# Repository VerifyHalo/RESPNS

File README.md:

# RESPonsive Neuro Stimulator

A public subset of our private development repositories.

We (re)designed an epilepsy implant in the class of NeuroPace's RNS from catalog chips, with prototype boards at about $600 in parts (60x cheaper), and run in vivo experiments to find the most effective treatment techniques.

### Background 

About 50 million people live with epilepsy, and 1 in 3 do not respond to medication. For many of them, the most advanced option is responsive neurostimulation: a real-time "surgeon" in the skull that listens to the brain (tissue), catches a seizure as it starts, and disrupts it with a short burst of stimulation. NeuroPace's RNS System, designed in the early 2000s and approved by the FDA in 2013, is still the only one, at about $37,000 for the system. It runs on a sealed, non-rechargeable cell; today's low-power chips and wireless charging make a redesign possible. In the long-term trial, patients had a median of 75% fewer seizures after 9 years.

Responsive neurostimulation (RNS) systems must be fully implanted because percutaneous components pose an infection risk, while emerging non-invasive data acquisition systems cannot match the signal quality of invasive techniques. So the battery is sealed in and every microamp counts. That is why devices like this have relied on custom chips.

### Redesign

Research prototype for bench and animal work. Not for human use.

Copyright © 2026 Anton Melnychuk. Licensed under the CERN Open Hardware Licence v2, Strongly Reciprocal (CERN-OHL-S-2.0); see LICENSE.

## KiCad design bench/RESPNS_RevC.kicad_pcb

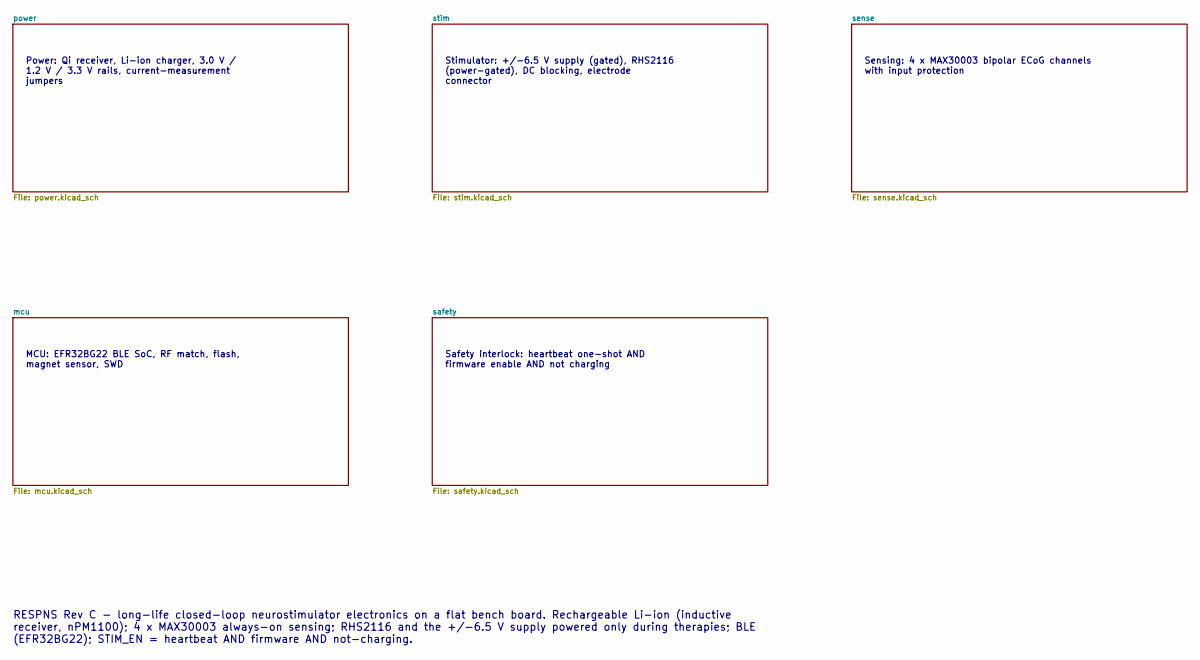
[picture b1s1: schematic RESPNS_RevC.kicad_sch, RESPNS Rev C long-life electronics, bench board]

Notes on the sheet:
Power: Qi receiver, Li-ion charger, 3.0 V / 1.2 V / 3.3 V rails, current-measurement jumpers
Stimulator: +/-6.5 V supply (gated), RHS2116 (power-gated), DC blocking, electrode connector
Sensing: 4 x MAX30003 bipolar ECoG channels with input protection
MCU: EFR32BG22 BLE SoC, RF match, flash, magnet sensor, SWD
Safety interlock: heartbeat one-shot AND firmware enable AND not charging
RESPNS Rev C - long-life closed-loop neurostimulator electronics on a flat bench board. Rechargeable Li-ion (inductive receiver, nPM1100); 4 x MAX30003 always-on sensing; RHS2116 and the +/-6.5 V supply powered only during therapies; BLE (EFR32BG22); STIM_EN = heartbeat AND firmware AND not-chargin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

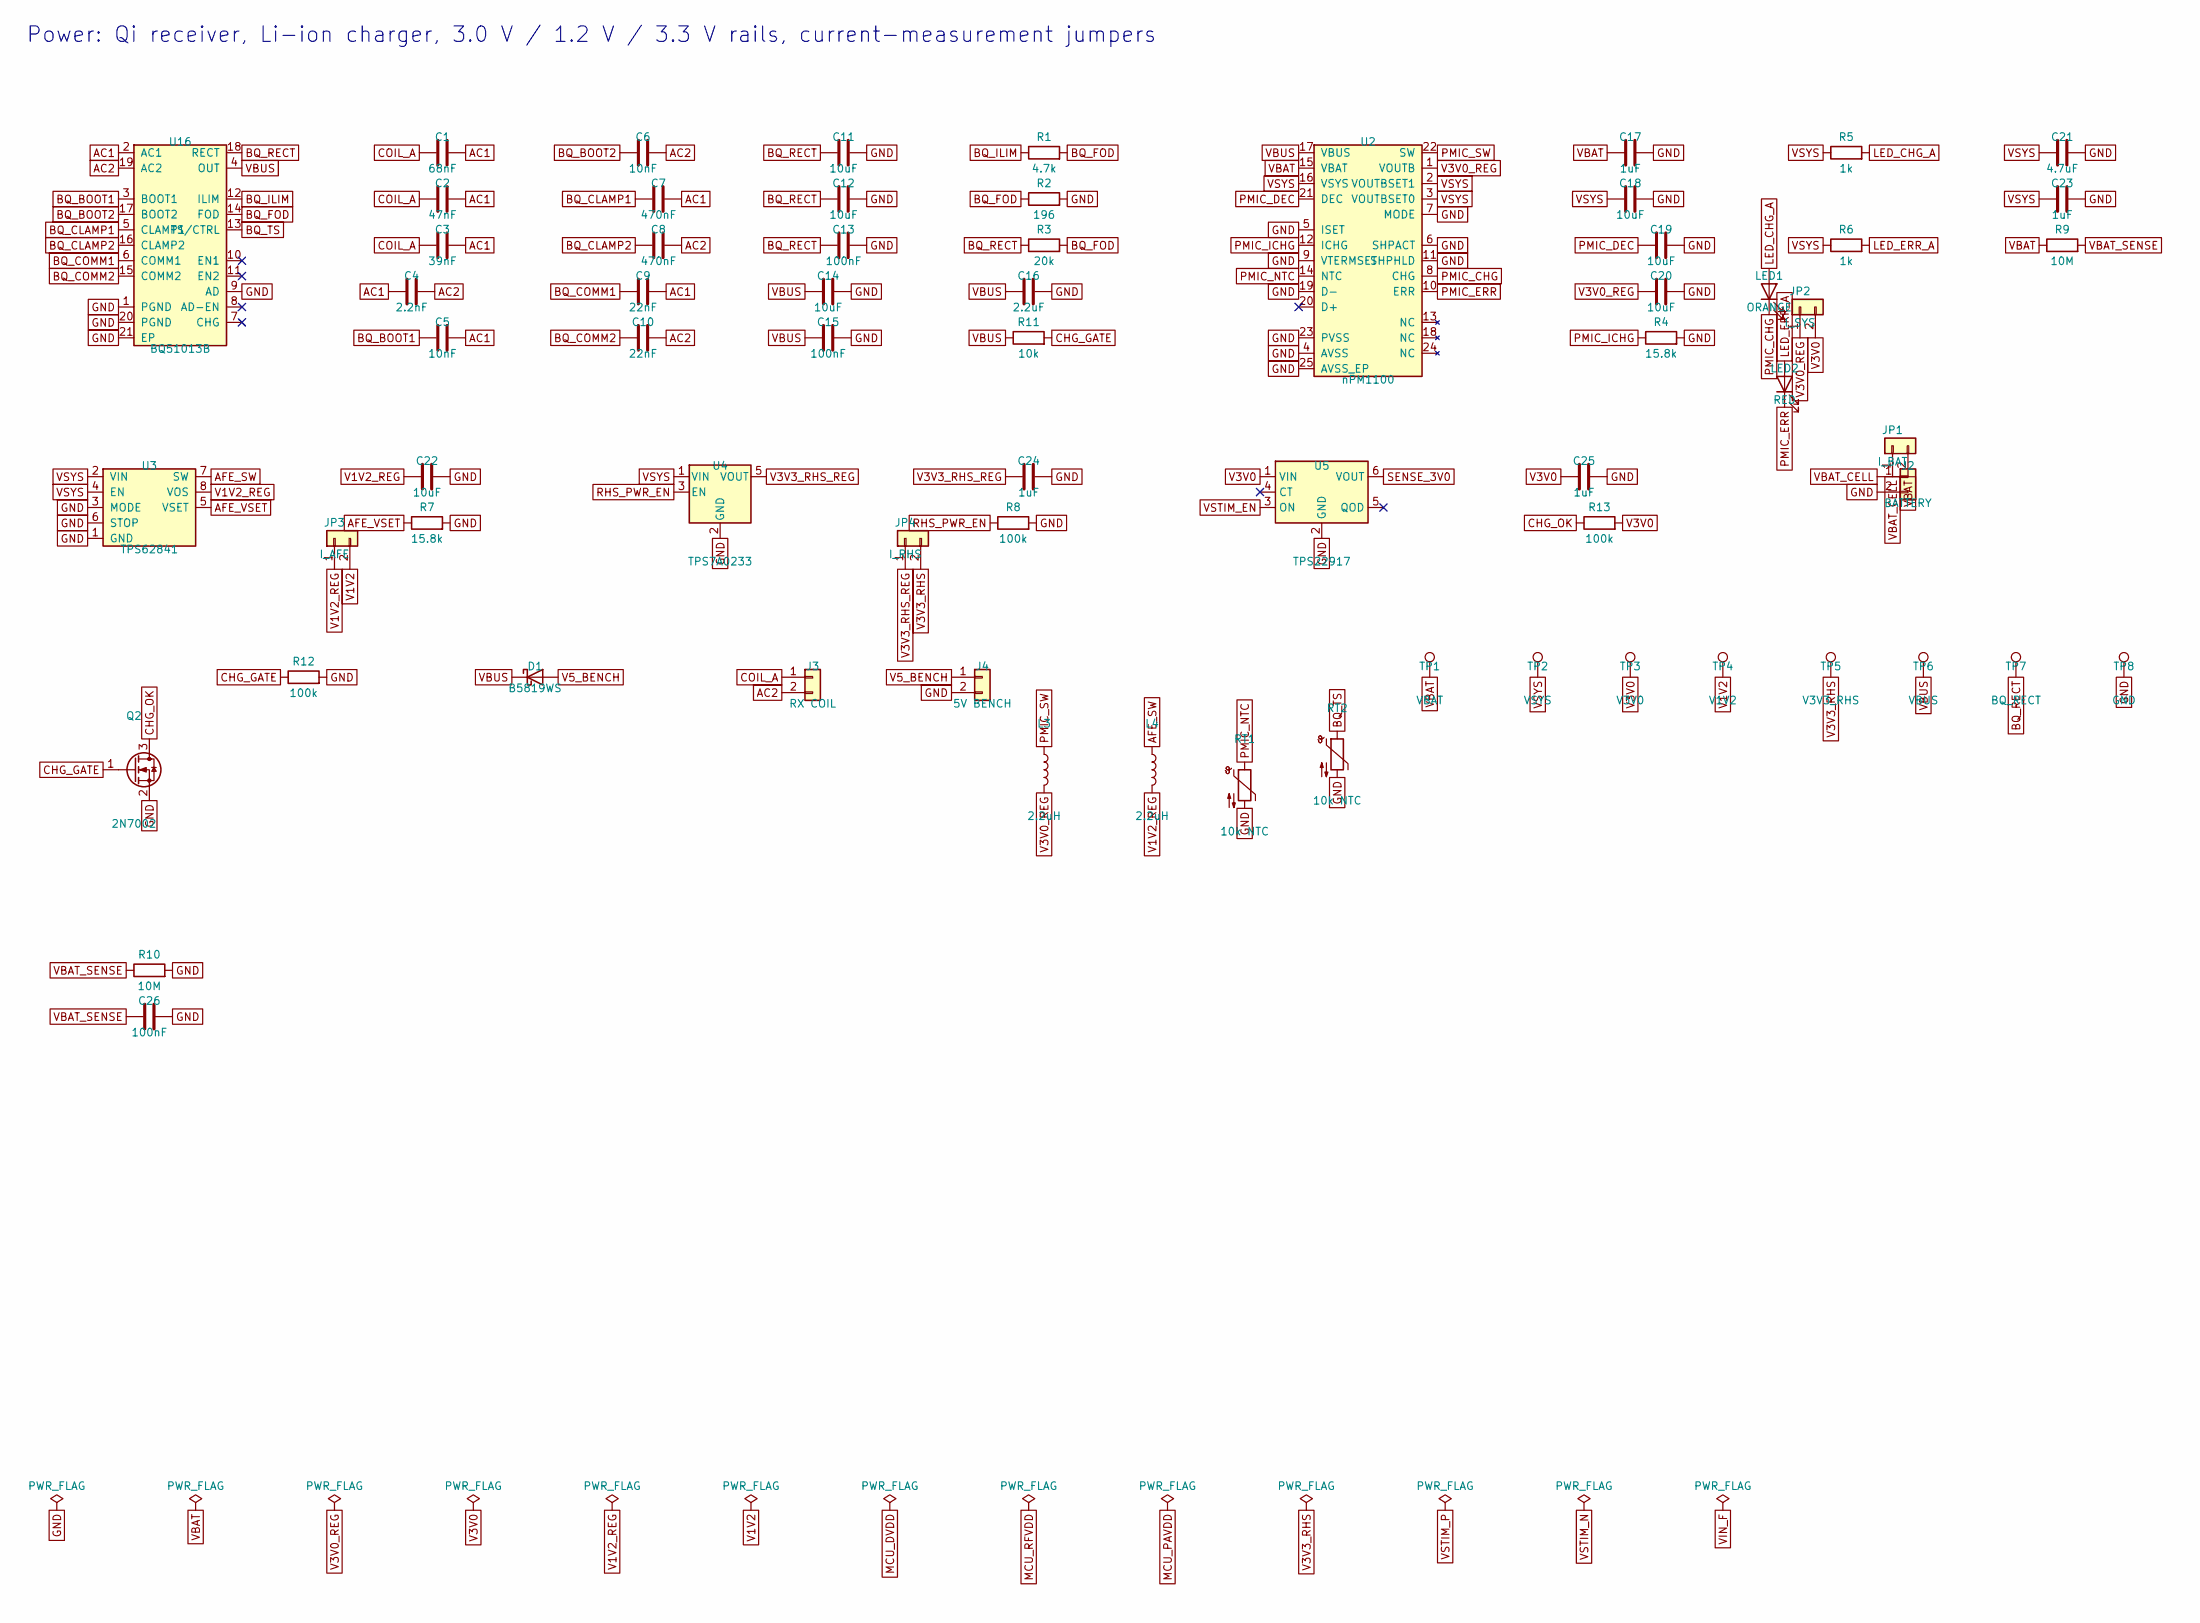
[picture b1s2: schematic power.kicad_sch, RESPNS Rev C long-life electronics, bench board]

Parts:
C1: 68nF; C_0603_1608Metric; MPN CL10B683KB8NNNC
C2: 47nF; C_0603_1608Metric; MPN CL10B473KB8NNNC
C3: 39nF; C_0603_1608Metric; MPN CL10B393KB8NNNC
C4: 2.2nF; C_0603_1608Metric; MPN CL10C222JB8NNNC
C5, C6: 10nF; C_0603_1608Metric; MPN CL10B103KB8NNNC
C7, C8: 470nF; C_0603_1608Metric; MPN CL10B474KA8NNNC
C9, C10: 22nF; C_0603_1608Metric; MPN CL10B223KB8NNNC
C11, C12, C14: 10uF; C_0805_2012Metric; MPN CL21A106KAYNNNE
C13, C15: 100nF; C_0603_1608Metric; MPN CL10B104KA8NNNC
C16: 2.2uF; C_0805_2012Metric; MPN CL21A225KAFNNNE
C17, C23, C24, C25: 1uF; C_0402_1005Metric; MPN CL05A105KA5NQNC
C18, C19, C20, C22: 10uF; C_0603_1608Metric; MPN CL10A106KP8NNNC
C21: 4.7uF; C_0603_1608Metric; MPN CL10A475KO8NNNC
C26: 100nF; C_0402_1005Metric; MPN CL05B104KO5NNNC
D1: B5819WS; D_SOD-323; MPN B5819WS
J2: BATTERY; JST_PH_S2B-PH-SM4-TB_1x02-1MP_P2.00mm_Horizontal; MPN S2B-PH-SM4-TB(LF)(SN)
J3: RX COIL; JST_SH_SM02B-SRSS-TB_1x02-1MP_P1.00mm_Horizontal; MPN SM02B-SRSS-TB(LF)(SN)
J4: 5V BENCH; PinHeader_1x02_P2.54mm_Vertical; MPN PZ254V-11-02P
JP1: I_BAT; PinHeader_1x02_P2.54mm_Vertical; MPN PZ254V-11-02P
JP2: I_SYS; PinHeader_1x02_P2.54mm_Vertical; MPN PZ254V-11-02P
JP3: I_AFE; PinHeader_1x02_P2.54mm_Vertical; MPN PZ254V-11-02P
JP4: I_RHS; PinHeader_1x02_P2.54mm_Vertical; MPN PZ254V-11-02P
L3, L4: 2.2uH; L_Changjiang_FTC201607S; MPN FTC201607S2R2MBCA
LED1: ORANGE; LED_0603_1608Metric; MPN 19-217/S2C-AL1M2VY/6T
LED2: RED; LED_0603_1608Metric; MPN 19-217/R6C-AL1M2VY/6T
Q2: 2N7002; SOT-23; MPN 2N7002
R1: 4.7k; R_0402_1005Metric; MPN 0402WGF4701TCE
R2: 196; R_0402_1005Metric; MPN 0402WGF1960TCE
R3: 20k; R_0402_1005Metric; MPN 0402WGF2002TCE
R4, R7: 15.8k; R_0402_1005Metric; MPN 0402WGF1582TCE
R5, R6: 1k; R_0402_1005Metric; MPN 0402WGF1001TCE
R8, R12, R13: 100k; R_0402_1005Metric; MPN 0402WGF1003TCE
R9, R10: 10M; R_0402_1005Metric; MPN 0402WGF1005TCE
R11: 10k; R_0402_1005Metric; MPN 0402WGF1002TCE
RT1, RT2: 10k NTC; R_0402_1005Metric; MPN NCP15XH103F03RC
TP1: VBAT; TestPoint_Pad_D1.0mm
TP2: VSYS; TestPoint_Pad_D1.0mm
TP3: V3V0; TestPoint_Pad_D1.0mm
TP4: V1V2; TestPoint_Pad_D1.0mm
TP5: V3V3_RHS; TestPoint_Pad_D1.0mm
TP6: VBUS; TestPoint_Pad_D1.0mm
TP7: BQ_RECT; TestPoint_Pad_D1.0mm
TP8: GND; TestPoint_Pad_D1.0mm
U2: nPM1100; QFN-24-1EP_4x4mm_P0.5mm_EP2.6x2.6mm_ThermalVias; MPN NPM1100-QDAA-R7
U3: TPS62841; VSON-8_1.5x2mm_P0.5mm; MPN TPS62841DLCR
U4: TPS7A0233; SOT-23-5; MPN TPS7A0233PDBVR
U5: TPS22917; SOT-23-6; MPN TPS22917DBVR
U16: BQ51013B; Texas_VQFN-RHL-20_ThermalVias; MPN BQ51013BRHLR

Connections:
AC1: C1.2, C2.2, C3.2, C4.1, C5.2, C7.2, C9.2, U16.2 (AC1)
AC2: C4.2, C6.2, C8.2, C10.2, J3.2, U16.19 (AC2)
AFE_SW: L4.1, U3.7 (SW)
AFE_VSET: R7.1, U3.5 (VSET)
BQ_BOOT1: C5.1, U16.3 (BOOT1)
BQ_BOOT2: C6.1, U16.17 (BOOT2)
BQ_CLAMP1: C7.1, U16.5 (CLAMP1)
BQ_CLAMP2: C8.1, U16.16 (CLAMP2)
BQ_COMM1: C9.1, U16.6 (COMM1)
BQ_COMM2: C10.1, U16.15 (COMM2)
BQ_FOD: R1.2, R2.1, R3.2, U16.14 (FOD)
BQ_ILIM: R1.1, U16.12 (ILIM)
BQ_RECT: C11.1, C12.1, C13.1, R3.1, TP7.1, U16.18 (RECT)
BQ_TS: RT2.1, U16.13 (TS/CTRL)
CHG_GATE: Q2.1 (G), R11.2, R12.1
CHG_OK: Q2.3 (D), R13.1; also elsewhere on the board
COIL_A: C1.1, C2.1, C3.1, J3.1
GND: C11.2, C12.2, C13.2, C14.2, C15.2, C16.2, C17.2, C18.2, C19.2, C20.2, C21.2, C22.2, C23.2, C24.2, C25.2, C26.2, J2.2, J4.2, Q2.2 (S), R2.2, R4.2, R7.2, R8.2, R10.2, R12.2, RT1.2, RT2.2, TP8.1, U2.4 (AVSS), U2.5 (ISET), U2.6 (SHPACT), U2.7 (MODE), U2.9 (VTERMSET), U2.11 (SHPHLD), U2.19 (D-), U2.23 (PVSS), U2.25 (AVSS_EP), U3.1 (GND), U3.3 (MODE), U3.6 (STOP), U4.2 (GND), U5.2 (GND), U16.1 (PGND), U16.9 (AD), U16.20 (PGND), U16.21 (EP); also elsewhere on the board
LED_CHG_A: LED1.2 (A), R5.2
LED_ERR_A: LED2.2 (A), R6.2
PMIC_CHG: LED1.1 (K), U2.8 (CHG)
PMIC_DEC: C19.1, U2.21 (DEC)
PMIC_ERR: LED2.1 (K), U2.10 (ERR)
PMIC_ICHG: R4.1, U2.12 (ICHG)
PMIC_NTC: RT1.1, U2.14 (NTC)
PMIC_SW: L3.1, U2.22 (SW)
RHS_PWR_EN: R8.1, U4.3 (EN); also elsewhere on the board
SENSE_3V0: U5.6 (VOUT); also elsewhere on the board
V1V2: JP3.2, TP4.1; also elsewhere on the board
V1V2_REG: C22.1, JP3.1, L4.2, U3.8 (VOS)
V3V0: C25.1, JP2.2, R13.2, TP3.1, U5.1 (VIN); also elsewhere on the board
V3V0_REG: C20.1, JP2.1, L3.2, U2.1 (VOUTB)
V3V3_RHS: JP4.2, TP5.1; also elsewhere on the board
V3V3_RHS_REG: C24.1, JP4.1, U4.5 (VOUT)
V5_BENCH: D1.2 (A), J4.1
VBAT: C17.1, JP1.2, R9.1, TP1.1, U2.15 (VBAT)
VBAT_CELL: J2.1, JP1.1
VBAT_SENSE: C26.1, R9.2, R10.1; also elsewhere on the board
VBUS: C14.1, C15.1, C16.1, D1.1 (K), R11.1, TP6.1, U2.17 (VBUS), U16.4 (OUT)
VSTIM_EN: U5.3 (ON); also elsewhere on the board
VSYS: C18.1, C21.1, C23.1, R5.1, R6.1, TP2.1, U2.2 (VOUTBSET1), U2.3 (VOUTBSET0), U2.16 (VSYS), U3.2 (VIN), U3.4 (EN), U4.1 (VIN); also elsewhere on the board

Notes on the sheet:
Power: Qi receiver, Li-ion charger, 3.0 V / 1.2 V / 3.3 V rails, current-measurement jumpers

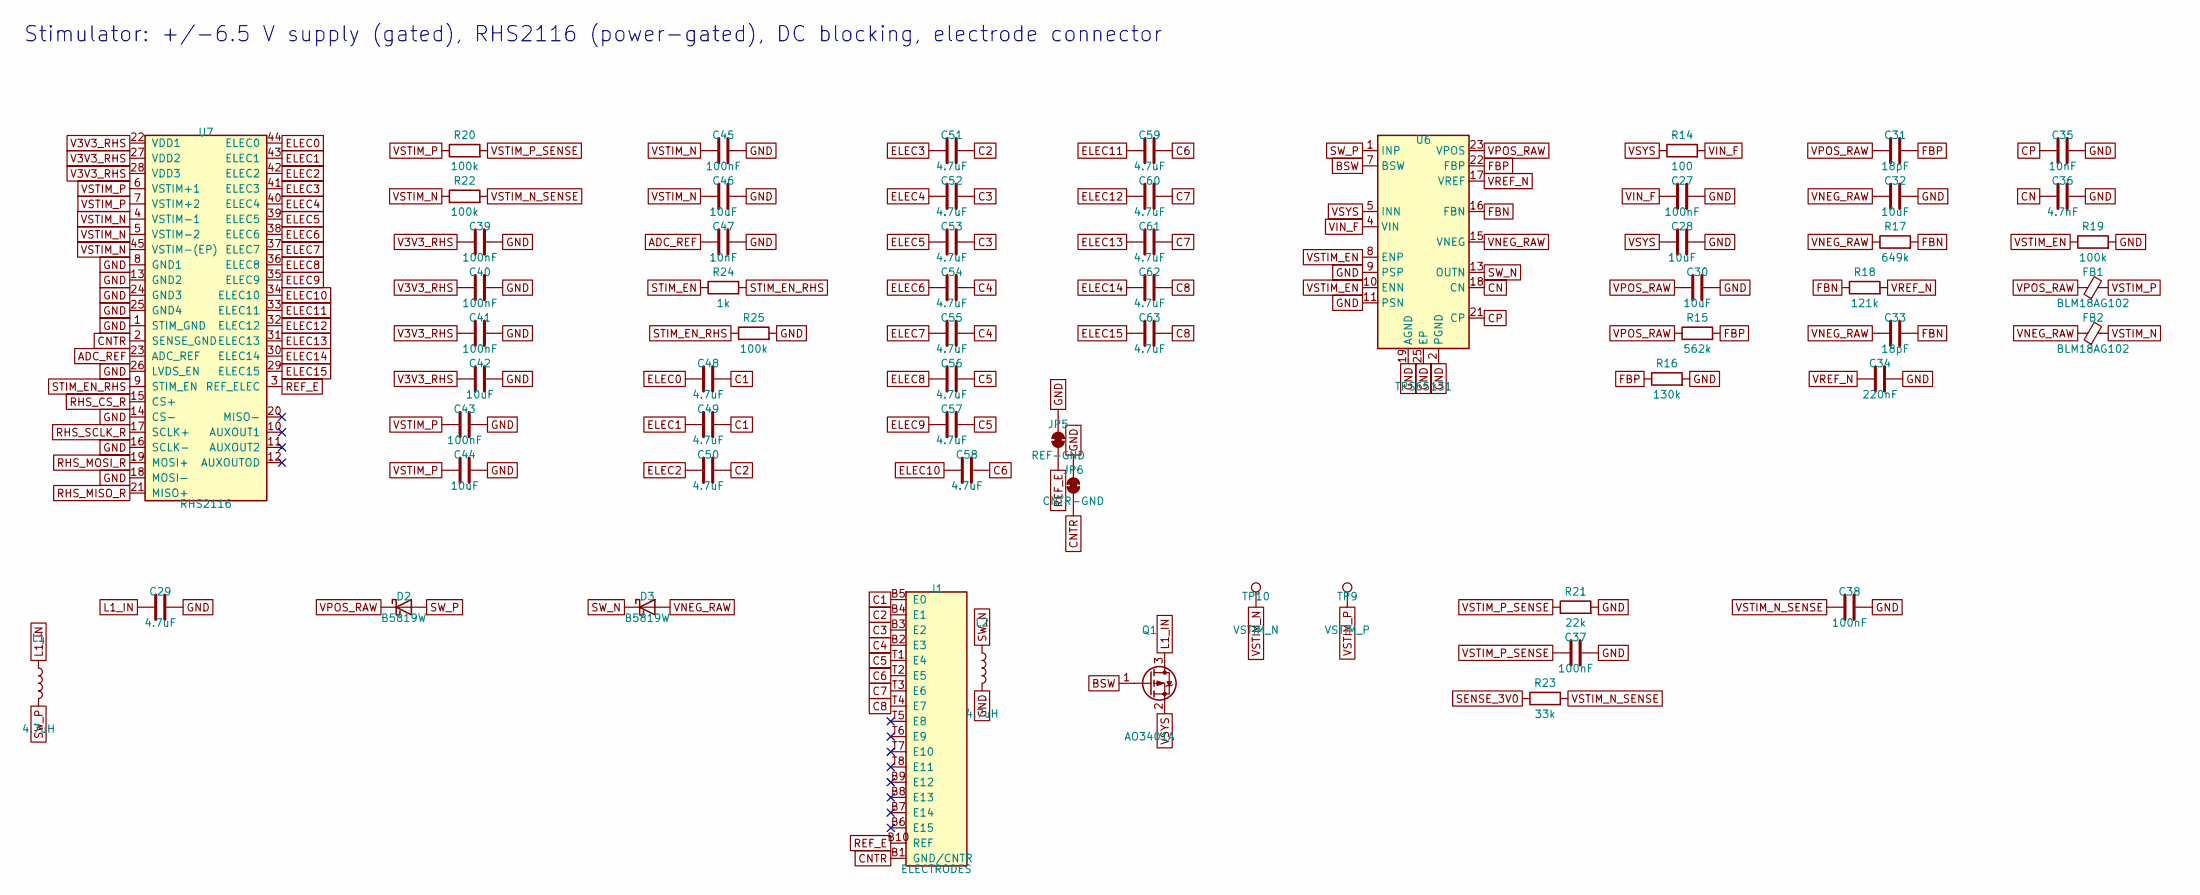
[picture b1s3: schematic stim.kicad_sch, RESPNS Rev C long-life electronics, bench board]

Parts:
C27, C37, C38, C39, C40, C41, C43, C45: 100nF; C_0402_1005Metric; MPN CL05B104KO5NNNC
C28, C42: 10uF; C_0603_1608Metric; MPN CL10A106KP8NNNC
C29: 4.7uF; C_0603_1608Metric; MPN CL10A475KO8NNNC
C30, C32, C44, C46: 10uF; C_0805_2012Metric; MPN CL21A106KAYNNNE
C31, C33: 18pF; C_0402_1005Metric; MPN CL05C180JB5NNNC
C34: 220nF; C_0402_1005Metric; MPN CL05A224KA5NNNC
C35, C47: 10nF; C_0402_1005Metric; MPN CL05B103KB5NNNC
C36: 4.7nF; C_0402_1005Metric; MPN CL05B472KB5NNNC
C48, C49, C50, C51, C52, C53, C54, C55, C56, C57, C58, C59, C60, C61, C62, C63: 4.7uF; C_0805_2012Metric; MPN CL21A475KAQNNNE
D2, D3: B5819W; D_SOD-123; MPN B5819W
FB1, FB2: BLM18AG102; L_0603_1608Metric; MPN BLM18AG102SN1D
J1: ELECTRODES; Omnetics_A79041_Intan16; MPN A79041-001
JP5: REF-GND; SolderJumper-2_P1.3mm_Bridged_RoundedPad1.0x1.5mm
JP6: CNTR-GND; SolderJumper-2_P1.3mm_Bridged_RoundedPad1.0x1.5mm
L1, L2: 4.7uH; L_Sunlord_SWPA4020S; MPN SWPA4020S4R7MT
Q1: AO3401A; SOT-23; MPN AO3401A
R14: 100; R_0402_1005Metric; MPN 0402WGF1000TCE
R15: 562k; R_0402_1005Metric; MPN CQ02WGF5623TCE
R16: 130k; R_0402_1005Metric; MPN 0402WGF1303TCE
R17: 649k; R_0402_1005Metric; MPN 0402WGF6493TCE
R18: 121k; R_0402_1005Metric; MPN 0402WGF1213TCE
R19, R20, R22, R25: 100k; R_0402_1005Metric; MPN 0402WGF1003TCE
R21: 22k; R_0402_1005Metric; MPN 0402WGF2202TCE
R23: 33k; R_0402_1005Metric; MPN 0402WGF3302TCE
R24: 1k; R_0402_1005Metric; MPN 0402WGF1001TCE
TP9: VSTIM_P; TestPoint_Pad_D1.0mm
TP10: VSTIM_N; TestPoint_Pad_D1.0mm
U6: TPS65131; VQFN-24-1EP_4x4mm_P0.5mm_EP2.45x2.45mm_ThermalVias; MPN TPS65131RGER
U7: RHS2116; Intan_QFN-44_7x7mm_P0.5mm_EP4.1x4.1mm; MPN RHS2116 (QFN, D5716)

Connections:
ADC_REF: C47.1, U7.23 (ADC_REF)
BSW: Q1.1 (G), U6.7 (BSW)
C1: C48.2, C49.2, J1.B5 (E0); also elsewhere on the board
C2: C50.2, C51.2, J1.B4 (E1); also elsewhere on the board
C3: C52.2, C53.2, J1.B3 (E2); also elsewhere on the board
C4: C54.2, C55.2, J1.B2 (E3); also elsewhere on the board
C5: C56.2, C57.2, J1.T1 (E4); also elsewhere on the board
C6: C58.2, C59.2, J1.T2 (E5); also elsewhere on the board
C7: C60.2, C61.2, J1.T3 (E6); also elsewhere on the board
C8: C62.2, C63.2, J1.T4 (E7); also elsewhere on the board
CN: C36.1, U6.18 (CN)
CNTR: J1.B1 (GND/CNTR), JP6.1 (A), U7.2 (SENSE_GND)
CP: C35.1, U6.21 (CP)
ELEC0: C48.1, U7.44 (ELEC0)
ELEC1: C49.1, U7.43 (ELEC1)
ELEC2: C50.1, U7.42 (ELEC2)
ELEC3: C51.1, U7.41 (ELEC3)
ELEC4: C52.1, U7.40 (ELEC4)
ELEC5: C53.1, U7.39 (ELEC5)
ELEC6: C54.1, U7.38 (ELEC6)
ELEC7: C55.1, U7.37 (ELEC7)
ELEC8: C56.1, U7.36 (ELEC8)
ELEC9: C57.1, U7.35 (ELEC9)
ELEC10: C58.1, U7.34 (ELEC10)
ELEC11: C59.1, U7.33 (ELEC11)
ELEC12: C60.1, U7.32 (ELEC12)
ELEC13: C61.1, U7.31 (ELEC13)
ELEC14: C62.1, U7.30 (ELEC14)
ELEC15: C63.1, U7.29 (ELEC15)
FBN: C33.2, R17.2, R18.1, U6.16 (FBN)
FBP: C31.2, R15.2, R16.1, U6.22 (FBP)
GND: C27.2, C28.2, C29.2, C30.2, C32.2, C34.2, C35.2, C36.2, C37.2, C38.2, C39.2, C40.2, C41.2, C42.2, C43.2, C44.2, C45.2, C46.2, C47.2, JP5.2 (B), JP6.2 (B), L2.2, R16.2, R19.2, R21.2, R25.2, U6.2 (PGND), U6.3 (PGND), U6.9 (PSP), U6.11 (PSN), U6.19 (AGND), U6.25 (EP), U7.1 (STIM_GND), U7.8 (GND1), U7.13 (GND2), U7.14 (CS-), U7.16 (SCLK-), U7.18 (MOSI-), U7.24 (GND3), U7.25 (GND4), U7.26 (LVDS_EN); also elsewhere on the board
L1_IN: C29.1, L1.1, Q1.3 (D)
REF_E: J1.B10 (REF), JP5.1 (A), U7.3 (REF_ELEC)
RHS_CS_R: U7.15 (CS+); also elsewhere on the board
RHS_MISO_R: U7.21 (MISO+); also elsewhere on the board
RHS_MOSI_R: U7.19 (MOSI+); also elsewhere on the board
RHS_SCLK_R: U7.17 (SCLK+); also elsewhere on the board
SENSE_3V0: R23.1; also elsewhere on the board
STIM_EN: R24.1; also elsewhere on the board
STIM_EN_RHS: R24.2, R25.1, U7.9 (STIM_EN)
SW_N: D3.1 (K), L2.1, U6.13 (OUTN), U6.14 (OUTN)
SW_P: D2.2 (A), L1.2, U6.1 (INP), U6.24 (INP)
V3V3_RHS: C39.1, C40.1, C41.1, C42.1, U7.22 (VDD1), U7.27 (VDD2), U7.28 (VDD3); also elsewhere on the board
VIN_F: C27.1, R14.2, U6.4 (VIN)
VNEG_RAW: C32.1, C33.1, D3.2 (A), FB2.1, R17.1, U6.15 (VNEG)
VPOS_RAW: C30.1, C31.1, D2.1 (K), FB1.1, R15.1, U6.23 (VPOS)
VREF_N: C34.1, R18.2, U6.17 (VREF)
VSTIM_EN: R19.1, U6.8 (ENP), U6.10 (ENN); also elsewhere on the board
VSTIM_N: C45.1, C46.1, FB2.2, R22.1, TP10.1, U7.4 (VSTIM-1), U7.5 (VSTIM-2), U7.45 (VSTIM-(EP))
VSTIM_N_SENSE: C38.1, R22.2, R23.2; also elsewhere on the board
VSTIM_P: C43.1, C44.1, FB1.2, R20.1, TP9.1, U7.6 (VSTIM+1), U7.7 (VSTIM+2)
VSTIM_P_SENSE: C37.1, R20.2, R21.1; also elsewhere on the board
VSYS: C28.1, Q1.2 (S), R14.1, U6.5 (INN), U6.6 (INN); also elsewhere on the board

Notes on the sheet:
Stimulator: +/-6.5 V supply (gated), RHS2116 (power-gated), DC blocking, electrode connector

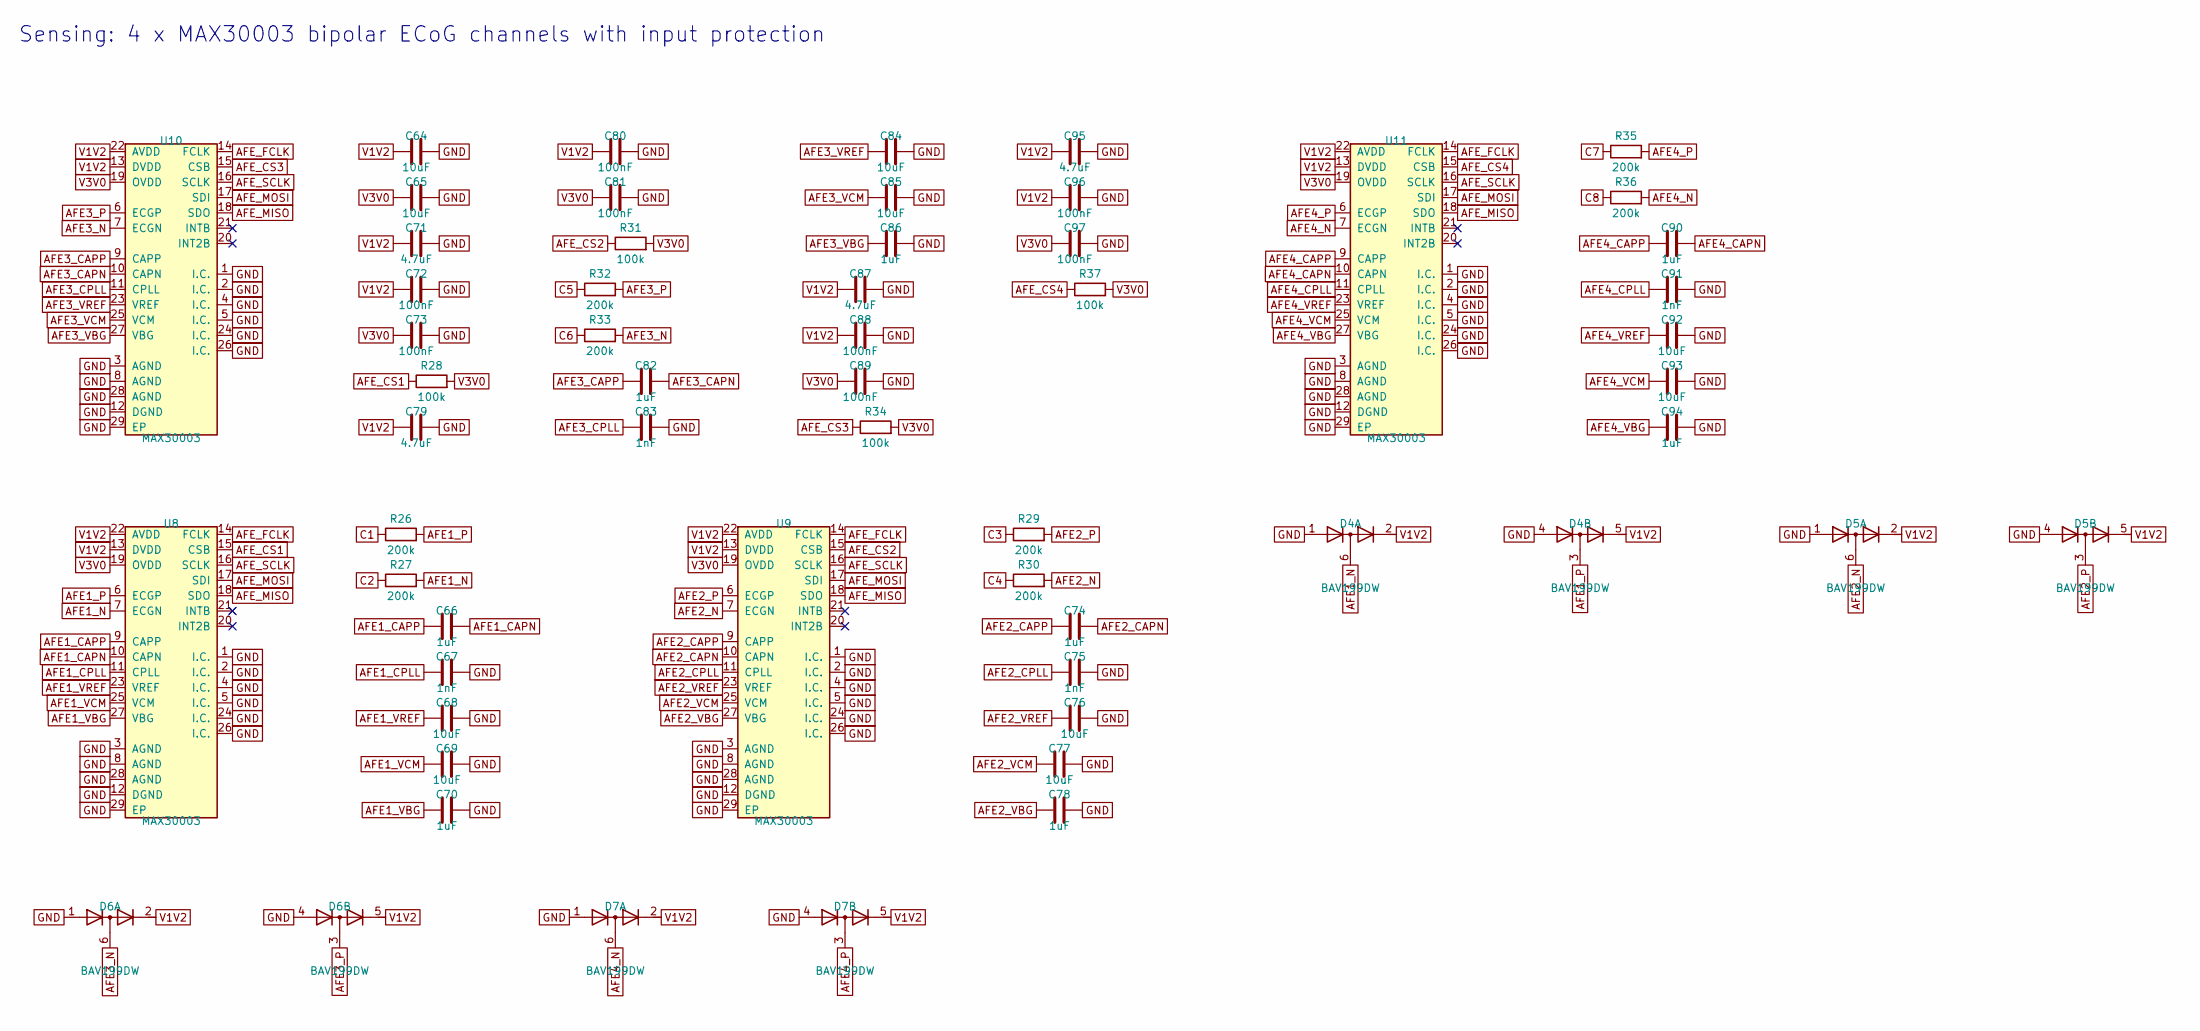
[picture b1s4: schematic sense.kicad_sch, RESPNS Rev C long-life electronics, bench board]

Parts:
C64, C65, C68, C69, C76, C77, C84, C85, C92, C93: 10uF; C_0603_1608Metric; MPN CL10A106KP8NNNC
C66, C70, C74, C78, C82, C86, C90, C94: 1uF; C_0402_1005Metric; MPN CL05A105KA5NQNC
C67, C75, C83, C91: 1nF; C_0402_1005Metric; MPN CL05C102JB5NNNC
C71, C79, C87, C95: 4.7uF; C_0603_1608Metric; MPN CL10A475KO8NNNC
C72, C73, C80, C81, C88, C89, C96, C97: 100nF; C_0402_1005Metric; MPN CL05B104KO5NNNC
D4, D5, D6, D7: BAV199DW; SOT-363_SC-70-6; MPN BAV199DW-7-F
R26, R27, R29, R30, R32, R33, R35, R36: 200k; R_0402_1005Metric; MPN 0402WGF2003TCE
R28, R31, R34, R37: 100k; R_0402_1005Metric; MPN 0402WGF1003TCE
U8, U9, U10, U11: MAX30003; QFN-28-1EP_5x5mm_P0.5mm_EP3.25x3.25mm_ThermalVias; MPN MAX30003CTI+

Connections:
AFE1_CAPN: C66.2, U8.10 (CAPN)
AFE1_CAPP: C66.1, U8.9 (CAPP)
AFE1_CPLL: C67.1, U8.11 (CPLL)
AFE1_N: D4.6 (K3A4), R27.2, U8.7 (ECGN)
AFE1_P: D4.3 (K1A2), R26.2, U8.6 (ECGP)
AFE1_VBG: C70.1, U8.27 (VBG)
AFE1_VCM: C69.1, U8.25 (VCM)
AFE1_VREF: C68.1, U8.23 (VREF)
AFE2_CAPN: C74.2, U9.10 (CAPN)
AFE2_CAPP: C74.1, U9.9 (CAPP)
AFE2_CPLL: C75.1, U9.11 (CPLL)
AFE2_N: D5.6 (K3A4), R30.2, U9.7 (ECGN)
AFE2_P: D5.3 (K1A2), R29.2, U9.6 (ECGP)
AFE2_VBG: C78.1, U9.27 (VBG)
AFE2_VCM: C77.1, U9.25 (VCM)
AFE2_VREF: C76.1, U9.23 (VREF)
AFE3_CAPN: C82.2, U10.10 (CAPN)
AFE3_CAPP: C82.1, U10.9 (CAPP)
AFE3_CPLL: C83.1, U10.11 (CPLL)
AFE3_N: D6.6 (K3A4), R33.2, U10.7 (ECGN)
AFE3_P: D6.3 (K1A2), R32.2, U10.6 (ECGP)
AFE3_VBG: C86.1, U10.27 (VBG)
AFE3_VCM: C85.1, U10.25 (VCM)
AFE3_VREF: C84.1, U10.23 (VREF)
AFE4_CAPN: C90.2, U11.10 (CAPN)
AFE4_CAPP: C90.1, U11.9 (CAPP)
AFE4_CPLL: C91.1, U11.11 (CPLL)
AFE4_N: D7.6 (K3A4), R36.2, U11.7 (ECGN)
AFE4_P: D7.3 (K1A2), R35.2, U11.6 (ECGP)
AFE4_VBG: C94.1, U11.27 (VBG)
AFE4_VCM: C93.1, U11.25 (VCM)
AFE4_VREF: C92.1, U11.23 (VREF)
AFE_CS1: R28.1, U8.15 (CSB); also elsewhere on the board
AFE_CS2: R31.1, U9.15 (CSB); also elsewhere on the board
AFE_CS3: R34.1, U10.15 (CSB); also elsewhere on the board
AFE_CS4: R37.1, U11.15 (CSB); also elsewhere on the board
AFE_FCLK: U8.14 (FCLK), U9.14 (FCLK), U10.14 (FCLK), U11.14 (FCLK); also elsewhere on the board
AFE_MISO: U8.18 (SDO), U9.18 (SDO), U10.18 (SDO), U11.18 (SDO); also elsewhere on the board
AFE_MOSI: U8.17 (SDI), U9.17 (SDI), U10.17 (SDI), U11.17 (SDI); also elsewhere on the board
AFE_SCLK: U8.16 (SCLK), U9.16 (SCLK), U10.16 (SCLK), U11.16 (SCLK); also elsewhere on the board
C1: R26.1; also elsewhere on the board
C2: R27.1; also elsewhere on the board
C3: R29.1; also elsewhere on the board
C4: R30.1; also elsewhere on the board
C5: R32.1; also elsewhere on the board
C6: R33.1; also elsewhere on the board
C7: R35.1; also elsewhere on the board
C8: R36.1; also elsewhere on the board
GND: C64.2, C65.2, C67.2, C68.2, C69.2, C70.2, C71.2, C72.2, C73.2, C75.2, C76.2, C77.2, C78.2, C79.2, C80.2, C81.2, C83.2, C84.2, C85.2, C86.2, C87.2, C88.2, C89.2, C91.2, C92.2, C93.2, C94.2, C95.2, C96.2, C97.2, D4.1 (A1), D4.4 (A3), D5.1 (A1), D5.4 (A3), D6.1 (A1), D6.4 (A3), D7.1 (A1), D7.4 (A3), U8.1 (I.C.), U8.2 (I.C.), U8.3 (AGND), U8.4 (I.C.), U8.5 (I.C.), U8.8 (AGND), U8.12 (DGND), U8.24 (I.C.), U8.26 (I.C.), U8.28 (AGND), U8.29 (EP), U9.1 (I.C.), U9.2 (I.C.), U9.3 (AGND), U9.4 (I.C.), U9.5 (I.C.), U9.8 (AGND), U9.12 (DGND), U9.24 (I.C.), U9.26 (I.C.), U9.28 (AGND), U9.29 (EP), U10.1 (I.C.), U10.2 (I.C.), U10.3 (AGND), U10.4 (I.C.), U10.5 (I.C.), U10.8 (AGND), U10.12 (DGND), U10.24 (I.C.), U10.26 (I.C.), U10.28 (AGND), U10.29 (EP), U11.1 (I.C.), U11.2 (I.C.), U11.3 (AGND), U11.4 (I.C.), U11.5 (I.C.), U11.8 (AGND), U11.12 (DGND), U11.24 (I.C.), U11.26 (I.C.), U11.28 (AGND), U11.29 (EP); also elsewhere on the board
V1V2: C64.1, C71.1, C72.1, C79.1, C80.1, C87.1, C88.1, C95.1, C96.1, D4.2 (K2), D4.5 (K4), D5.2 (K2), D5.5 (K4), D6.2 (K2), D6.5 (K4), D7.2 (K2), D7.5 (K4), U8.13 (DVDD), U8.22 (AVDD), U9.13 (DVDD), U9.22 (AVDD), U10.13 (DVDD), U10.22 (AVDD), U11.13 (DVDD), U11.22 (AVDD); also elsewhere on the board
V3V0: C65.1, C73.1, C81.1, C89.1, C97.1, R28.2, R31.2, R34.2, R37.2, U8.19 (OVDD), U9.19 (OVDD), U10.19 (OVDD), U11.19 (OVDD); also elsewhere on the board

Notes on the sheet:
Sensing: 4 x MAX30003 bipolar ECoG channels with input protection

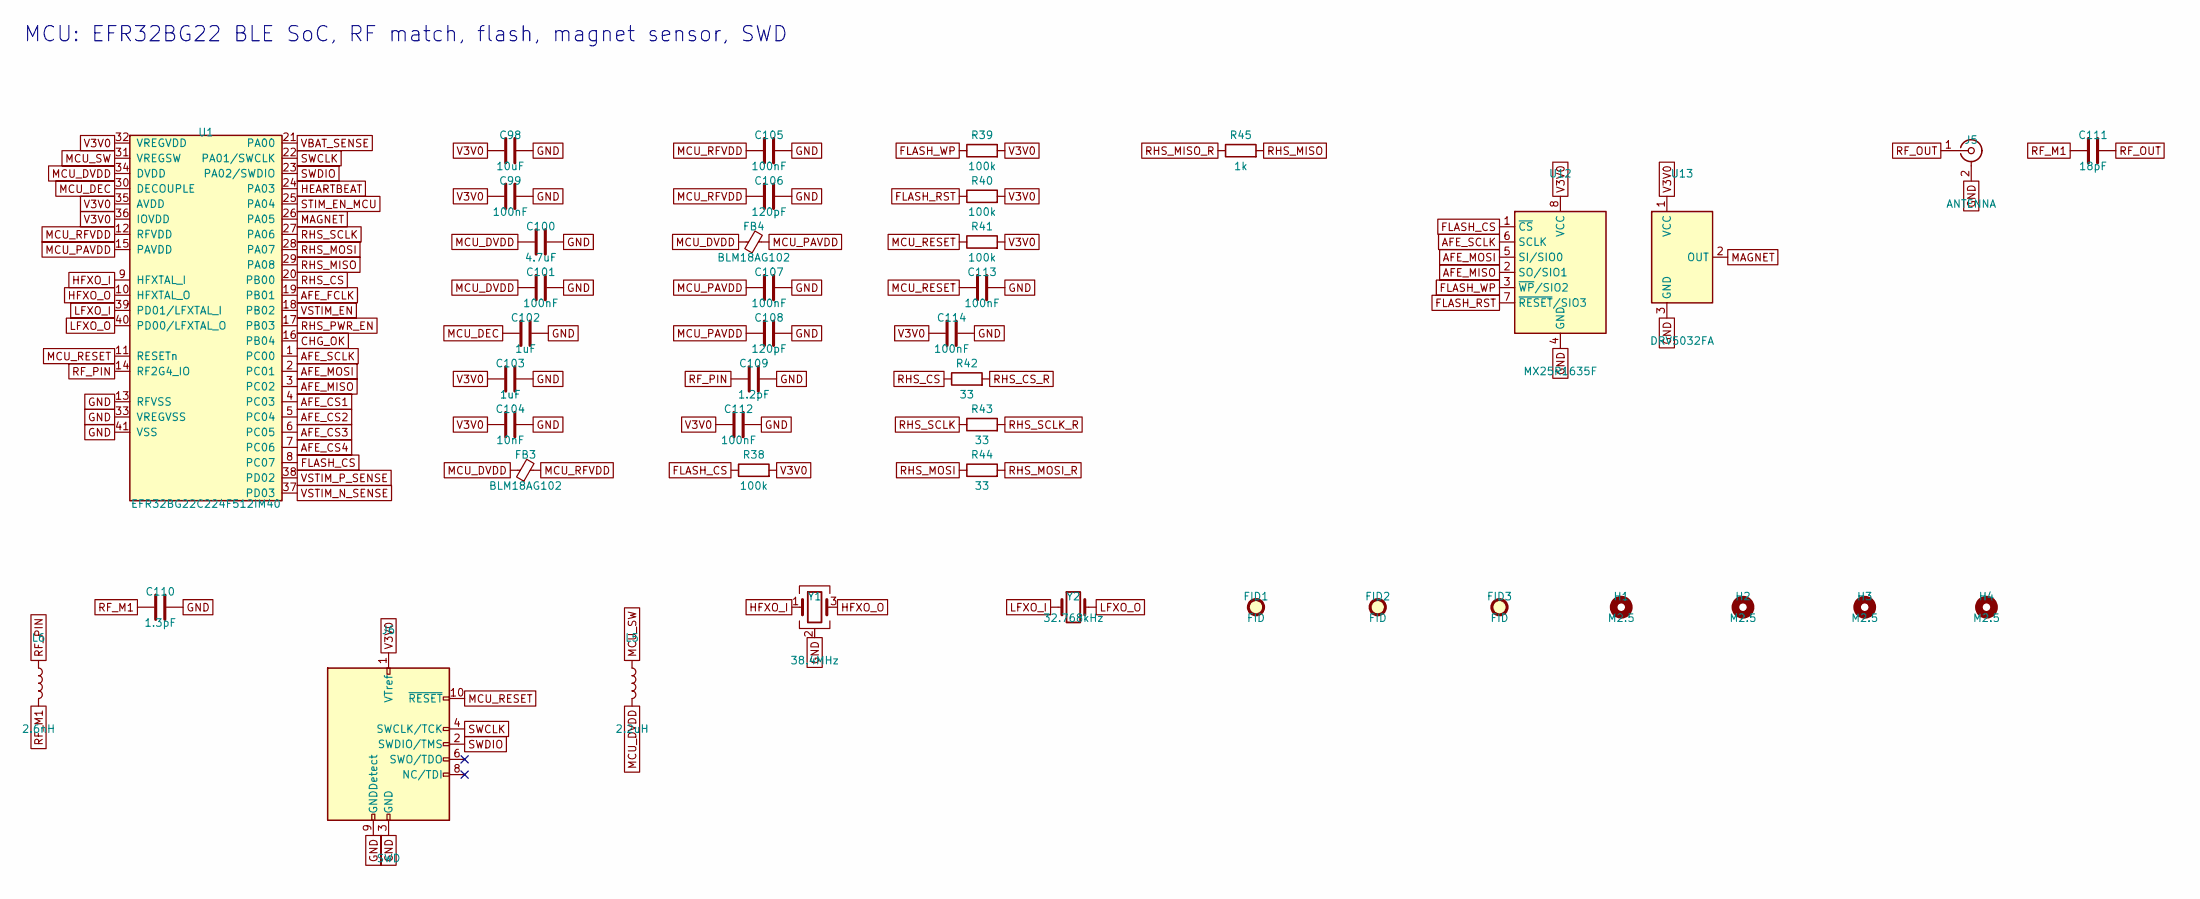
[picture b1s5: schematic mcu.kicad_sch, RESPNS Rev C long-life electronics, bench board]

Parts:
C98: 10uF; C_0603_1608Metric; MPN CL10A106KP8NNNC
C99, C101, C105, C107, C112, C113, C114: 100nF; C_0402_1005Metric; MPN CL05B104KO5NNNC
C100: 4.7uF; C_0603_1608Metric; MPN CL10A475KO8NNNC
C102, C103: 1uF; C_0402_1005Metric; MPN CL05A105KA5NQNC
C104: 10nF; C_0402_1005Metric; MPN CL05B103KB5NNNC
C106, C108: 120pF; C_0402_1005Metric; MPN CL05C121JB5NNNC
C109: 1.2pF; C_0402_1005Metric; MPN GRM1555C1H1R2WA01D
C110: 1.3pF; C_0402_1005Metric; MPN GRM1555C1H1R3WA01D
C111: 18pF; C_0402_1005Metric; MPN CL05C180JB5NNNC
FB3, FB4: BLM18AG102; L_0603_1608Metric; MPN BLM18AG102SN1D
FID1, FID2, FID3: FID; Fiducial_1mm_Mask2mm
H1, H2, H3, H4: M2.5; MountingHole_2.7mm_M2.5
J5: ANTENNA; U.FL_Hirose_U.FL-R-SMT-1_Vertical; MPN U.FL-R-SMT-1(10)
J6: SWD; PinHeader_2x05_P1.27mm_Vertical_SMD; MPN FTSH-105-01-F-DV-K
L5: 2.2uH; L_1008_2520Metric; MPN FTC252012S2R2MBCA
L6: 2.6nH; L_0402_1005Metric; MPN LQW15AN2N6B8ZD
R38, R39, R40, R41: 100k; R_0402_1005Metric; MPN 0402WGF1003TCE
R42, R43, R44: 33; R_0402_1005Metric; MPN 0402WGF330JTCE
R45: 1k; R_0402_1005Metric; MPN 0402WGF1001TCE
U1: EFR32BG22C224F512IM40; QFN-40-1EP_5x5mm_P0.4mm_EP3.6x3.6mm_ThermalVias; MPN EFR32BG22C224F512IM40-C
U12: MX25R1635F; SOIC-8_3.9x4.9mm_P1.27mm; MPN MX25R1635FM1IL0
U13: DRV5032FA; SOT-23; MPN DRV5032FADBZR
Y1: 38.4MHz; Crystal_SMD_2016-4Pin_2.0x1.6mm; MPN X201638MSB4SI
Y2: 32.768kHz; Crystal_SMD_2012-2Pin_2.0x1.2mm; MPN FC-12M 32.768KHZ 9PF

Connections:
AFE_CS1: U1.4 (PC03); also elsewhere on the board
AFE_CS2: U1.5 (PC04); also elsewhere on the board
AFE_CS3: U1.6 (PC05); also elsewhere on the board
AFE_CS4: U1.7 (PC06); also elsewhere on the board
AFE_FCLK: U1.19 (PB01); also elsewhere on the board
AFE_MISO: U1.3 (PC02), U12.2 (SO/SIO1); also elsewhere on the board
AFE_MOSI: U1.2 (PC01), U12.5 (SI/SIO0); also elsewhere on the board
AFE_SCLK: U1.1 (PC00), U12.6 (SCLK); also elsewhere on the board
CHG_OK: U1.16 (PB04); also elsewhere on the board
FLASH_CS: R38.1, U1.8 (PC07), U12.1 (~CS)
FLASH_RST: R40.1, U12.7 (~RESET/SIO3)
FLASH_WP: R39.1, U12.3 (~WP/SIO2)
GND: C98.2, C99.2, C100.2, C101.2, C102.2, C103.2, C104.2, C105.2, C106.2, C107.2, C108.2, C109.2, C110.2, C112.2, C113.2, C114.2, J5.2 (Ext), J6.3 (GND), J6.5 (GND), J6.9 (GNDDetect), U1.13 (RFVSS), U1.33 (VREGVSS), U1.41 (VSS), U12.4 (GND), U13.3 (GND), Y1.2 (G), Y1.4 (G); also elsewhere on the board
HEARTBEAT: U1.24 (PA03); also elsewhere on the board
HFXO_I: U1.9 (HFXTAL_I), Y1.1
HFXO_O: U1.10 (HFXTAL_O), Y1.3
LFXO_I: U1.39 (PD01/LFXTAL_I), Y2.1
LFXO_O: U1.40 (PD00/LFXTAL_O), Y2.2
MAGNET: U1.26 (PA05), U13.2 (OUT)
MCU_DEC: C102.1, U1.30 (DECOUPLE)
MCU_DVDD: C100.1, C101.1, FB3.1, FB4.1, L5.2, U1.34 (DVDD)
MCU_PAVDD: C107.1, C108.1, FB4.2, U1.15 (PAVDD)
MCU_RESET: C113.1, J6.10 (~RESET), R41.1, U1.11 (RESETn)
MCU_RFVDD: C105.1, C106.1, FB3.2, U1.12 (RFVDD)
MCU_SW: L5.1, U1.31 (VREGSW)
RF_M1: C110.1, C111.1, L6.2
RF_OUT: C111.2, J5.1 (In)
RF_PIN: C109.1, L6.1, U1.14 (RF2G4_IO)
RHS_CS: R42.1, U1.20 (PB00)
RHS_CS_R: R42.2; also elsewhere on the board
RHS_MISO: R45.2, U1.29 (PA08)
RHS_MISO_R: R45.1; also elsewhere on the board
RHS_MOSI: R44.1, U1.28 (PA07)
RHS_MOSI_R: R44.2; also elsewhere on the board
RHS_PWR_EN: U1.17 (PB03); also elsewhere on the board
RHS_SCLK: R43.1, U1.27 (PA06)
RHS_SCLK_R: R43.2; also elsewhere on the board
STIM_EN_MCU: U1.25 (PA04); also elsewhere on the board
SWCLK: J6.4 (SWCLK/TCK), U1.22 (PA01/SWCLK)
SWDIO: J6.2 (SWDIO/TMS), U1.23 (PA02/SWDIO)
V3V0: C98.1, C99.1, C103.1, C104.1, C112.1, C114.1, J6.1 (VTref), R38.2, R39.2, R40.2, R41.2, U1.32 (VREGVDD), U1.35 (AVDD), U1.36 (IOVDD), U12.8 (VCC), U13.1 (VCC); also elsewhere on the board
VBAT_SENSE: U1.21 (PA00); also elsewhere on the board
VSTIM_EN: U1.18 (PB02); also elsewhere on the board
VSTIM_N_SENSE: U1.37 (PD03); also elsewhere on the board
VSTIM_P_SENSE: U1.38 (PD02); also elsewhere on the board

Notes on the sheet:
MCU: EFR32BG22 BLE SoC, RF match, flash, magnet sensor, SWD
